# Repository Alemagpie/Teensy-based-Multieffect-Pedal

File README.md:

#DESCRIPTION:
A simple, microcontroller-based, multieffect pedal for guitar. The processing is done with a Teensy 4.1 microcontroller paired with an Audio Shield extension card.

#CURRENT PROGRESS:
-> Elemental DSP modules that can be combined to create all sorts of effects (gain, mixer, filters, lfo, drive, delay line, quantizer, sample and hold, etc.).

- Distortion effect with 4 parameters (gain, bias, treble, volume)
- Tremolo effect with 3 parameters (frequency, shape, depth)
- Bitcrusher effect with 4 parameters (resolution, down-sampling, mix, low pass)
- Vibrato effect with 3 parameters (speed, depth, tone)
- Chorus effect with 4 parameters (speed, depth, voices, mix)
- Delay with 4 parameters (time, feedback, dry, wet)
- Envelope filter (QTron style) with 4 parameters (sensibility, resonance, attack/release, filter type)
- Ring modulator with 4 parameters (frequency, shape, depth, mix)
- Square wave octaver with 4 parameters (dry, same octave, down octave, low-pass filter)

- Ability to chain multiple effects simultaneously
- Ability to change parameters' values in real time
- Ability to change effects in the chain
- simple UI

#TO-DO:
- Fix phaser
- Add makeup gain to all effects

#ROADMAP:
- Allpass filter module
- Replace pots with rotary encoder
- Add expression pedal input and parameter assign button
- Use one of the main switches as a momentary hold switch
- Add tap tempo 

#FUTURE EFFECTS:
- Ducking delay
- LFO lp
- Phaser
- Reverb
- Ambient drone (pads)
- ADSR envelope follower
- EQ
- Compressor
- Flanger
- Octaver
- Shimmer
- Wavefolder
- Granular

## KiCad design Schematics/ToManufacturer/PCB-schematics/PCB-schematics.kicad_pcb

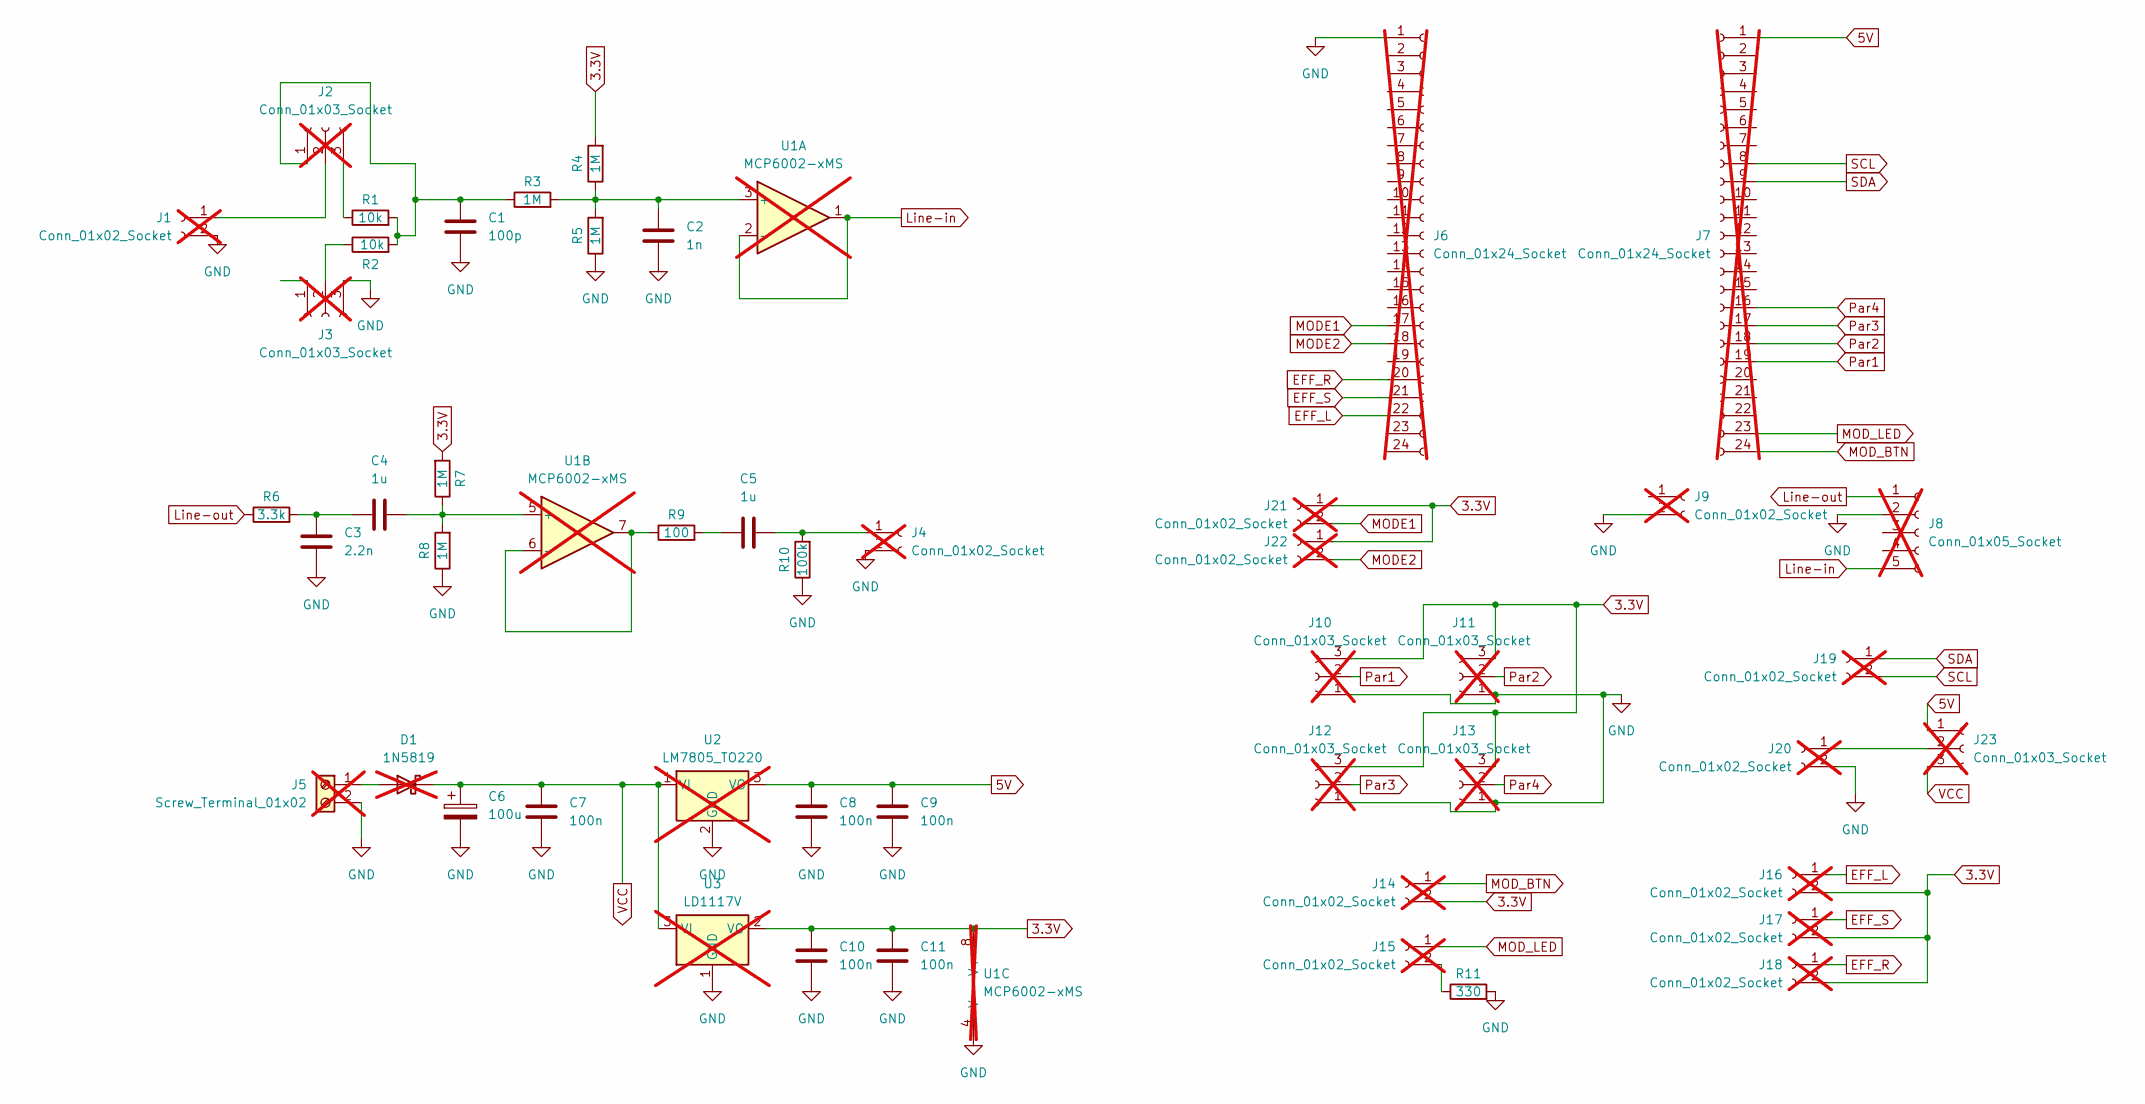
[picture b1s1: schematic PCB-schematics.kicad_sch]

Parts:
C1: 100p; C_0603_1608Metric
C2: 1n; C_0603_1608Metric
C3: 2.2n; C_0603_1608Metric
C4, C5: 1u; C_0603_1608Metric
C6: 100u; C_0603_1608Metric
C7, C8, C9, C10, C11: 100n; C_0603_1608Metric
D1: 1N5819; D_DO-41_SOD81_P10.16mm_Horizontal; not fitted
J1, J4, J14, J15, J16, J17, J18, J19, J20, J21, J22: Conn_01x02_Socket; JST_XH_B2B-XH-A_1x02_P2.50mm_Vertical; not fitted
J2, J3, J10, J11, J12, J13: Conn_01x03_Socket; JST_XH_B3B-XH-A_1x03_P2.50mm_Vertical; not fitted
J5: Screw_Terminal_01x02; TerminalBlock_MetzConnect_Type055_RT01502HDWU_1x02_P5.00mm_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; not fitted
J6, J7: Conn_01x24_Socket; PinSocket_1x24_P2.54mm_Vertical; not fitted
J8: Conn_01x05_Socket; Molex_SL_171971-0005_1x05_P2.54mm_Vertical; not fitted
J9: Conn_01x02_Socket; Molex_SL_171971-0002_1x02_P2.54mm_Vertical; not fitted
J23: Conn_01x03_Socket; PinSocket_1x03_P2.54mm_Vertical; not fitted
R1, R2: 10k; R_0603_1608Metric
R3, R4, R5, R7, R8: 1M; R_0603_1608Metric
R6: 3.3k; R_0603_1608Metric
R9: 100; R_0603_1608Metric
R10: 100k; R_0603_1608Metric
R11: 330; R_0603_1608Metric
U1: MCP6002-xMS; DIP-8_W7.62mm; not fitted
U2: LM7805_TO220; TO-220-3_Vertical; not fitted
U3: LD1117V; TO-220-3_Vertical; not fitted

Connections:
3.3V: C10.1, C11.1, J10.3, J11.3, J12.3, J13.3, J14.2, J16.2, J17.2, J18.2, J21.1, J22.1, R4.2, R7.2, U1.8 (V+), U3.2 (VO)
5V: C8.1, C9.1, J7.1, J23.1, U2.3 (VO)
EFF_L: J6.22, J16.1
EFF_R: J6.20, J18.1
EFF_S: J6.21, J17.1
GND: C1.2, C2.2, C3.2, C6.2, C7.2, C8.2, C9.2, C10.2, C11.2, J1.2, J3.3, J4.2, J5.2, J6.1, J8.2, J9.2, J10.1, J11.1, J12.1, J13.1, J20.2, R5.1, R8.1, R10.1, R11.2, U1.4 (V-), U2.2 (GND), U3.1 (GND)
Line-in: J8.5, U1.1, U1.2 (-)
Line-out: J8.1, R6.1
MODE1: J6.17, J21.2
MODE2: J6.18, J22.2
MOD_BTN: J7.24, J14.1
MOD_LED: J7.23, J15.1
unnamed: C3.1, C4.1, R6.2
unnamed: C5.1, R9.2
unnamed: D1.2 (A), J5.1
unnamed: J1.1, J2.2
unnamed: C1.1, J2.1, R1.2, R2.2, R3.1
unnamed: J2.3, R1.1
unnamed: J3.2, R2.1
unnamed: C5.2, J4.1, R10.2
unnamed: J15.2, R11.1
unnamed: J20.1, J23.2
unnamed: C2.1, R3.2, R4.1, R5.2, U1.3 (+)
unnamed: C4.2, R7.1, R8.2, U1.5 (+)
unnamed: R9.1, U1.6 (-), U1.7
Par1: J7.19, J10.2
Par2: J7.18, J11.2
Par3: J7.17, J12.2
Par4: J7.16, J13.2
SCL: J7.8, J19.2
SDA: J7.9, J19.1
VCC: C6.1, C7.1, D1.1 (K), J23.3, U2.1 (VI), U3.3 (VI)

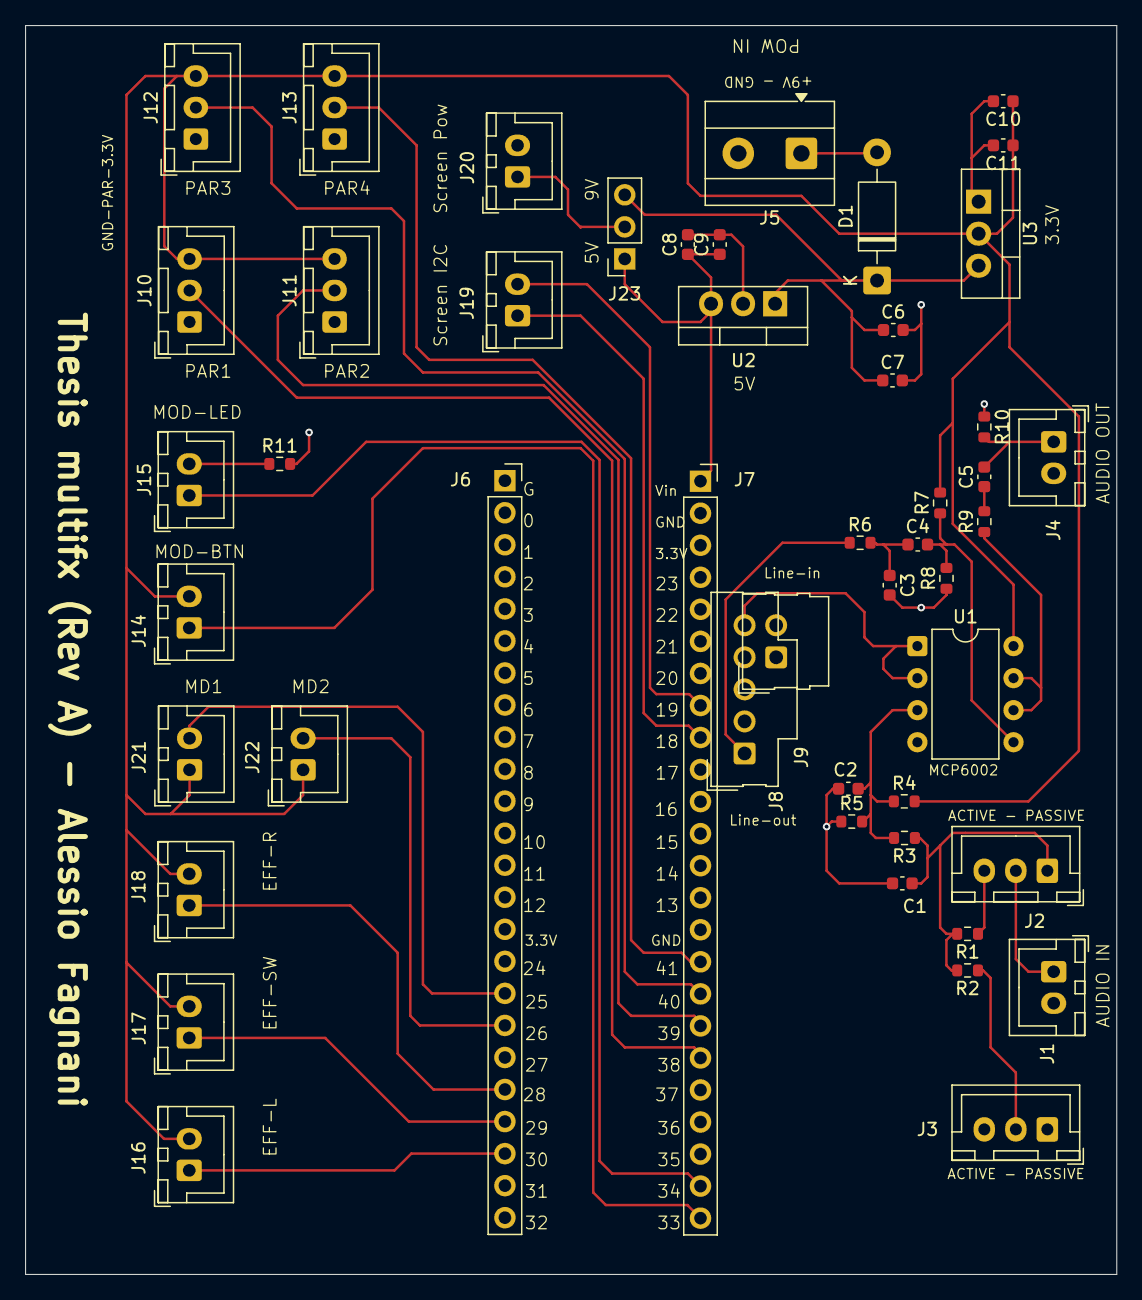
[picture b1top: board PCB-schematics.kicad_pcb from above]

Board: 2 copper layers, 86.5 x 99.0 mm, 49 parts (0 on the bottom side), 32 nets.

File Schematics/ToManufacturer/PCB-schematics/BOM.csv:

"Reference","Qty","Value","DNP","Exclude from BOM","Exclude from Board","Footprint","Datasheet"
"C1","1","100p","","","","Capacitor_SMD:C_0603_1608Metric","~"
"C2","1","1n","","","","Capacitor_SMD:C_0603_1608Metric","~"
"C3","1","2.2n","","","","Capacitor_SMD:C_0603_1608Metric","~"
"C4,C5","2","1u","","","","Capacitor_SMD:C_0603_1608Metric","~"
"C6","1","100u","","","","Capacitor_Tantalum_SMD:CP_EIA-1608-08_AVX-J","~"
"C7,C8,C9,C10,C11","5","100n","","","","Capacitor_SMD:C_0603_1608Metric","~"
"D1","1","1N5819","DNP","Excluded from BOM","","Diode_THT:D_DO-41_SOD81_P10.16mm_Horizontal","http://www.vishay.com/docs/88525/1n5817.pdf"
"J1,J4,J14,J15,J16,J17,J18,J19,J20,J21,J22","11","Conn_01x02_Socket","DNP","Excluded from BOM","","Connector_JST:JST_XH_B2B-XH-A_1x02_P2.50mm_Vertical","~"
"J2,J3,J10,J11,J12,J13","6","Conn_01x03_Socket","DNP","Excluded from BOM","","Connector_JST:JST_XH_B3B-XH-A_1x03_P2.50mm_Vertical","~"
"J5","1","Screw_Terminal_01x02","DNP","Excluded from BOM","","TerminalBlock_MetzConnect:TerminalBlock_MetzConnect_Type055_RT01502HDWU_1x02_P5.00mm_Horizontal","~"
"J6,J7","2","Conn_01x24_Socket","DNP","Excluded from BOM","","Connector_PinSocket_2.54mm:PinSocket_1x24_P2.54mm_Vertical","~"
"J8","1","Conn_01x05_Socket","DNP","Excluded from BOM","","Connector_Molex:Molex_SL_171971-0005_1x05_P2.54mm_Vertical","~"
"J9","1","Conn_01x02_Socket","DNP","Excluded from BOM","","Connector_Molex:Molex_SL_171971-0002_1x02_P2.54mm_Vertical","~"
"J23","1","Conn_01x03_Socket","DNP","Excluded from BOM","","Connector_PinSocket_2.54mm:PinSocket_1x03_P2.54mm_Vertical","~"
"R1,R2","2","10k","","","","Resistor_SMD:R_0603_1608Metric","~"
"R3,R4,R5,R7,R8","5","1M","","","","Resistor_SMD:R_0603_1608Metric","~"
"R6","1","3.3k","","","","Resistor_SMD:R_0603_1608Metric","~"
"R9","1","100","","","","Resistor_SMD:R_0603_1608Metric","~"
"R10","1","100k","","","","Resistor_SMD:R_0603_1608Metric","~"
"R11","1","330","","","","Resistor_SMD:R_0603_1608Metric","~"
"U1","1","MCP6002-xMS","DNP","Excluded from BOM","","Package_DIP:DIP-8_W7.62mm","http://ww1.microchip.com/downloads/en/DeviceDoc/21733j.pdf"
"U2","1","LM7805_TO220","DNP","Excluded from BOM","","Package_TO_SOT_THT:TO-220-3_Vertical","https://www.onsemi.cn/PowerSolutions/document/MC7800-D.PDF"
"U3","1","LD1117V","DNP","Excluded from BOM","","Package_TO_SOT_THT:TO-220-3_Vertical","https://www.st.com/resource/en/datasheet/ld1117.pdf"

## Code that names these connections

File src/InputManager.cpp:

#include "InputManager.h"

void InputManager::begin() {
    for(int i = 0; i < 8; i++)
        edges[i] = 0;

    //expr btn = par3, clk = md1, dt = md2, enc pb = par1, expr ped = par2/4
        
    //tap tempo btn and led
    pinMode(SWITCH_X, INPUT_PULLDOWN);
    pinMode(MODIFY_L_PIN, OUTPUT);

    pinMode(PARAM1_PIN, INPUT_PULLUP); //encoder push button (par1)
    pinMode(PARAM2_PIN, INPUT_PULLDOWN); //...
    pinMode(PARAM3_PIN, INPUT_PULLDOWN); //expression assign button (par3)
    pinMode(PARAM4_PIN, INPUT); //expression pedal (par2/4)

    //Main switches
    pinMode(SWITCH_L, INPUT_PULLDOWN);
    pinMode(SWITCH_C, INPUT_PULLDOWN);
    pinMode(SWITCH_R, INPUT_PULLDOWN);

    //Encoder digital pins
    pinMode(MODE1_PIN, INPUT_PULLUP);   //encoder clk
    pinMode(MODE2_PIN, INPUT_PULLUP);   //encoder dt

    prev_CLK_state = digitalRead(MODE1_PIN);
}

void InputManager::update() {
    uint32_t now = millis();

    for(int i = 0; i < 6; i++) {
        buttons[i].update();

        if(i == 4) { //encoder push button -> pullup
            if(buttons[i].fallingEdge())
                edges[2*i] = millis();

            if(buttons[i].risingEdge()) 
                edges[2*i+1] = millis();

        } else { //any other button -> pulldown
            if(buttons[i].risingEdge())
                edges[2*i] = millis();

            if(buttons[i].fallingEdge()) 
                edges[2*i+1] = millis();

        }

        if(edges[2*i] != 0 && edges[2*i+1] != 0) {
            if(inputState.switches[i] != PressType::HOLD) {
                inputState.switches[i] = (edges[2*i+1] - edges[2*i] < LONG_PRESS_TIME_MS) ? PressType::SHORT : PressType::LONG;
            } else {
                inputState.switches[i] = PressType::NONE;
            }

            edges[2*i+1] = edges[2*i] = 0;
        } else {
            if(edges[2*i] != 0 && edges[2*i+1] == 0 && (now - edges[2*i] > HOLD_PRESS_TIME_MS)) {
                inputState.switches[i] = PressType::HOLD;
            } else {
                inputState.switches[i] = PressType::NONE;
            }
        }
    }

    //Encoder movement
    CLK_state = digitalRead(MODE1_PIN);
    if(CLK_state != prev_CLK_state && CLK_state == LOW) {
       inputState.encoderDelta = (digitalRead(MODE2_PIN) == LOW) ? 1 : -1;
    } else {
        inputState.encoderDelta = 0;
    }
    prev_CLK_state = CLK_state;
}

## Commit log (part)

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2025-10-31 Start
2025-11-01 Solved inheritance problem
2025-11-01 Added modified version of the Audio library
2025-11-01 Add Audio library as regular files
2025-11-02 Adapted chorus, created distortion, added basic control
2025-11-02 More implementation (faulty build)
2025-11-02 Fixed core errors (still chorus and dyn cast to fix)
2025-11-03 Small changes, chorus still broken
2025-11-03 Solved chorus issue
    The header and cpp needed to be moved to src/ to compile correctly (don't know exactly why tho)
2025-11-03 Chorus still broken, started implementing init fnc
2025-11-03 Another 1000 tries, same 2 errors
2025-11-03 Renamed EffectHandler (I'm losing my mind)
2025-11-03 Debugging (I'm losing my mind)
2025-11-03 Debug pt.2
2025-11-04 More debug
2025-11-06 Partial fix (?)
2025-11-06 Faulty build
2025-11-09 Initialize README with project details
    Add project description, to-do list, and planned features.
2025-11-09 README.md
    Expanded project description with details about the Teensy 4.1 microcontroller and Audio Shield.
2025-11-09 Added schematics
2025-11-10 Effects will be re-implemented manually
2025-11-11 Added tanh optimization
2025-11-24 Removed dyn cast + minor changes
2025-11-25 Massive changes to avoid float math
2025-11-25 Basic 1-pole filters
2025-11-25 Test with simpler main
    DistortionEffect works, needs some more work
2025-11-27 Fixes on lp and hp filters
2025-11-29 Started implementing tremolo
2025-11-30 Tested different distortions, fixed fastTanh
2025-12-02 Filter fixes, electric circuit fix (KiCad updated)
2025-12-05 hp/lp filters. input reading.
2025-12-07 First LFO implementation
2025-12-07 started LFO implementation
2025-12-08 LFO + tremolo implementation
2025-12-13 Implemented tremolo + minor fixes
2025-12-13 tremolo fixes + effect chain implem
2025-12-13 Added dist volume param
2025-12-26 Implemented uniform quantizer
2026-01-01 Schematics work
2026-02-01 Implemented bitcrusher (to fix)
2026-02-02 Implemented bitcrusher
    Fixed bitcrusher bugs, implemented all 4 parameters
2026-02-09 changes to LFO, started vibrato
2026-02-11 Implemented screen manager
2026-02-11 Implemented UI
2026-02-11 Started chorus implem (to fix)
2026-02-12 Implemented chorus
2026-02-14 Changes to vibrato
2026-03-09 Started refactoring + pcb schematic work
2026-03-09 More refactoring (only chorus left)
2026-03-10 More refactoring + bug fixes
2026-03-10 Refactoring
    Updated README to reflect current progress and to-do items.
2026-03-10 More modules and fixes
2026-03-13 LUT generator changes, start of ADSR impl, start of log params
2026-03-28 Cleanup and testing
2026-04-01 Final testing (vibrato and chorus pops to fix)
2026-04-02 Fixed fucking clicking in vibrato and chorus
2026-04-02 Made distortion and tremolo modular
2026-04-03 Refactoring, and cleanup
2026-04-08 Start of save system
2026-04-10 Finished save system, general cleanup
2026-04-12 Modify state bug fix + start of delay impl
2026-04-21 Start of biquad implem
2026-04-22 Biquad implem
2026-04-22 Cleanup in preparation for biquad filter
2026-04-22 Fixed delay line redundancy
2026-04-28 Added final thesis
